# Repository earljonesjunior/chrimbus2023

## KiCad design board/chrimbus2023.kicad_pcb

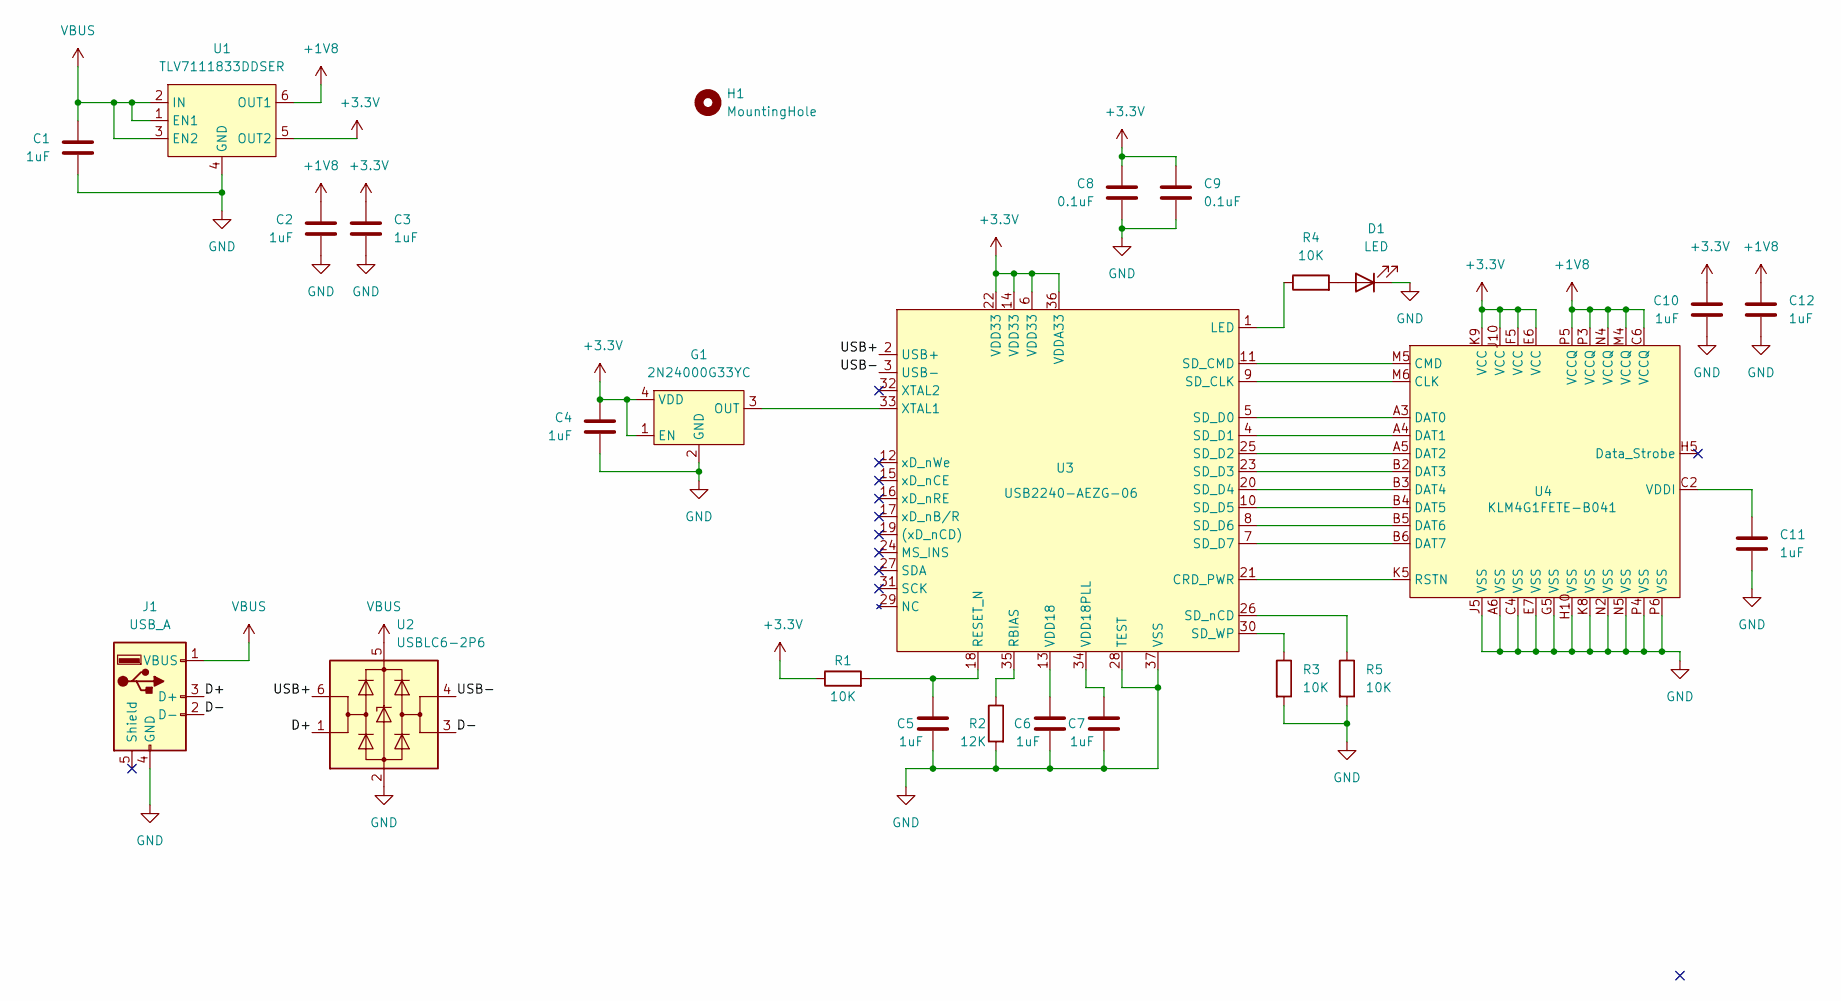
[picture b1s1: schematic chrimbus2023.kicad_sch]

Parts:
C1, C2, C3, C4, C5, C6, C7, C10, C11, C12: 1uF; C_0402_1005Metric; LCSC C14445
C8, C9: 0.1uF; C_0402_1005Metric; LCSC C1525
D1: LED; LED_1206_3216Metric_Pad1.42x1.75mm_HandSolder
G1: 2N24000G33YC; Oscillator_SMD_ECS_2520MV-xxx-xx-4Pin_2.5x2.0mm; LCSC C252326
H1: MountingHole; MountingHole_3.2mm_M3
J1: USB_A; usb-PCB
R1, R3, R4, R5: 10K; R_0402_1005Metric; LCSC C25744
R2: 12K; R_0402_1005Metric; LCSC C25752
U1: TLV7111833DDSER; WSON-6_1.5x1.5mm_P0.5mm; LCSC C75880
U2: USBLC6-2P6; SOT-666; LCSC C15999
U3: USB2240-AEZG-06; QFN-36-1EP_6x6mm_P0.5mm_EP4.1x4.1mm_ThermalVias; LCSC C633328
U4: KLM4G1FETE-B041; BGA153C50P14X14_1100X1000X80; LCSC C500273

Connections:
+1V8: C2.1, C12.1, U1.6 (OUT1), U4.C6 (VCCQ), U4.M4 (VCCQ), U4.N4 (VCCQ), U4.P3 (VCCQ), U4.P5 (VCCQ)
+3.3V: C3.1, C4.1, C8.1, C9.1, C10.1, G1.1 (EN), G1.4 (VDD), R1.1, U1.5 (OUT2), U3.6 (VDD33), U3.14 (VDD33), U3.22 (VDD33), U3.36 (VDDA33), U4.E6 (VCC), U4.F5 (VCC), U4.J10 (VCC), U4.K9 (VCC)
/D+: J1.3 (D+), U2.1 (I/O1)
/D-: J1.2 (D-), U2.3 (I/O2)
/USB+: U2.6 (I/O1), U3.2 (USB+)
/USB-: U2.4 (I/O2), U3.3 (USB-)
GND: C1.2, C2.2, C3.2, C4.2, C5.2, C6.2, C7.2, C8.2, C9.2, C10.2, C11.2, C12.2, D1.1 (K), G1.2 (GND), J1.4 (GND), R2.2, R3.2, R5.2, U1.4 (GND), U2.2 (GND), U3.28 (TEST), U3.37 (VSS), U4.A6 (VSS), U4.C4 (VSS), U4.E7 (VSS), U4.G5 (VSS), U4.H10 (VSS), U4.J5 (VSS), U4.K8 (VSS), U4.N2 (VSS), U4.N5 (VSS), U4.P4 (VSS), U4.P6 (VSS)
unnamed: D1.2 (A), R4.2
unnamed: G1.3 (OUT), U3.33 (XTAL1)
unnamed: U3.21 (CRD_PWR), U4.K5 (RSTN)
unnamed: R4.1, U3.1 (LED)
unnamed: R2.1, U3.35 (RBIAS)
unnamed: C5.1, R1.2, U3.18 (RESET_N)
unnamed: U3.9 (SD_CLK), U4.M6 (CLK)
unnamed: U3.11 (SD_CMD), U4.M5 (CMD)
unnamed: U3.5 (SD_D0), U4.A3 (DAT0)
unnamed: U3.4 (SD_D1), U4.A4 (DAT1)
unnamed: U3.25 (SD_D2), U4.A5 (DAT2)
unnamed: U3.23 (SD_D3), U4.B2 (DAT3)
unnamed: U3.20 (SD_D4), U4.B3 (DAT4)
unnamed: U3.10 (SD_D5), U4.B4 (DAT5)
unnamed: U3.8 (SD_D6), U4.B5 (DAT6)
unnamed: U3.7 (SD_D7), U4.B6 (DAT7)
unnamed: R3.1, U3.30 (SD_WP)
unnamed: R5.1, U3.26 (SD_nCD)
unnamed: C6.1, U3.13 (VDD18)
unnamed: C7.1, U3.34 (VDD18PLL)
unnamed: C11.1, U4.C2 (VDDI)
VBUS: C1.1, J1.1 (VBUS), U1.1 (EN1), U1.2 (IN), U1.3 (EN2), U2.5 (VBUS)

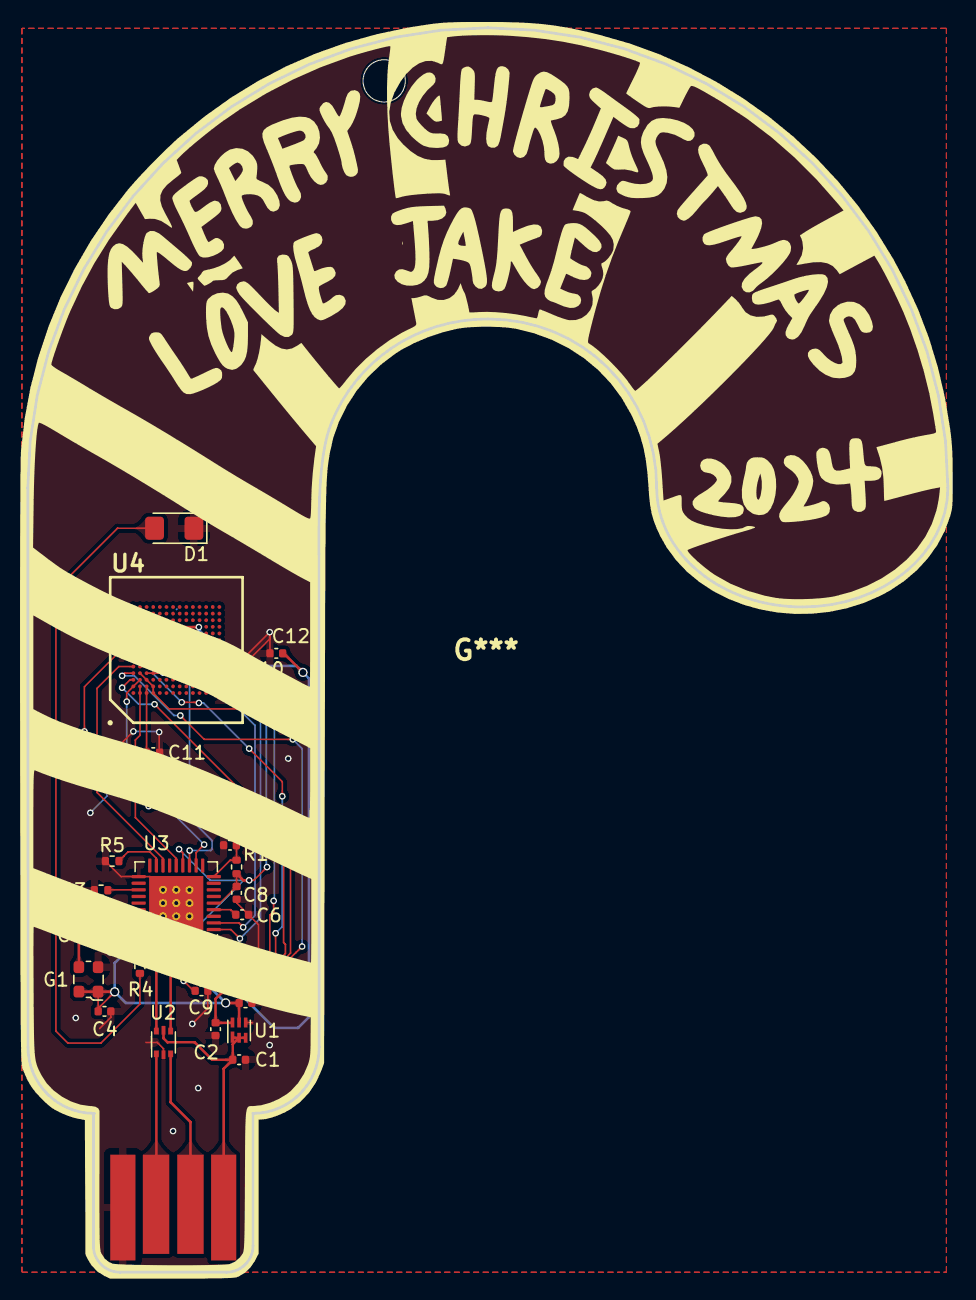
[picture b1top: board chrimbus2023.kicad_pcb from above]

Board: 2 copper layers, 69.5 x 94.0 mm, 25 parts (0 on the bottom side), 29 nets.

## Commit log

2023-12-09 initial
2023-12-09 ssh test
2023-12-10 almost done
2023-12-13 final
2025-11-29 2024
